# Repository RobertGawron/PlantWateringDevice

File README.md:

# Plant Watering Device

This is a device for watering indoor plants based on the 8-pin PIC10F202-IOT microcontroller.

The goal is to try to make a project on this small MCU and learn how to deal with the limitations of such a small chip, as well as to learn the PIC MCU family ecosystem.

Features:

* **Sensing soil humidity** using a cheap capacitance sensor
* **Display of actual soil humidity and low-level soil humidity when the watering is started;** what is presented on the display is selected by a button, and an additional two LEDs indicate the current reading shown on the display
* Possibility to **change the quantity of water that is dispersed when the soil is detected as dry;** the level can be modified via a button and the current setting is shown on a 10-segment LED bargraph
* Possibility to **select the moisture level when the soil is considered dry** and the watering should be started via a potentiometer

## Software

The software is written in C (C99 with _Static_assert from C11).

[Software details.](./Software/README.md)

## Formal Verification

The watering logic is formally verified using frama-c to mathematically prove correctness properties such as:

* Watering is **never activated** when soil moisture is above the threshold
* Watering **always stops** after the configured duration
* No integer overflows or out-of-bounds array accesses occur

This provides stronger guarantees than testing alone — instead of checking specific inputs, it exhaustively verifies **all possible** input combinations.

## Simulation

The software can be run in a web browser to speed up development (no need to flash the device, soil humidity can be simulated as wanted, etc.).

[Simulation details.](./Simulation/README.md)

## Hardware

[Hardware details.](./Hardware/README.md)

Design tools: KiCad

## Mechanical

In order to keep the pump, PCB, display, and potentiometer in one place, a simple 3D printed holder was made.

[Mechanical specifications and assembly details.](./Mechanic/README.md)

Design tools: OpenSCAD and FreeCad

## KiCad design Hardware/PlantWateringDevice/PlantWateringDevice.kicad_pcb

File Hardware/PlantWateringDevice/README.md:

# Purpose

This section describes the electronic circuit of this device.

# Tools

The circuit was made in KiCad.

# Used modules

These cheap modules were used in this device; they or their clones are available on AliExpress or similar sites:
* 0.28 Inch LED Digital Display DC Voltmeter 0-100V 2.5-30V
* JSB1523006 DC 5V 6V 030 Mini Vacuum Pump Air Pump Oxygen Pump Diaphragm Pump Current 80mA 60KPa 0.6L/min
* Capacitive Soil Moisture Sensor Module Corrosion Resistant Wide Voltage Wire Analog Capacitive Soil Moisture Sensor V1.2

# Electronic diagrams

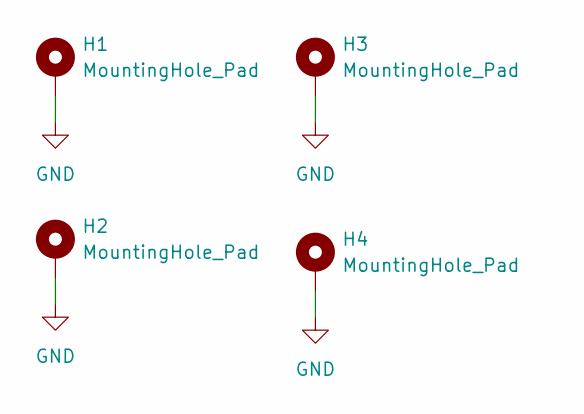
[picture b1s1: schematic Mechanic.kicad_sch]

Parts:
H1, H2, H3, H4: MountingHole_Pad; MountingHole_2.5mm_Pad

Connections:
GND: H1.1 (1_1), H2.1 (1_1), H3.1 (1_1), H4.1 (1_1); also elsewhere on the board

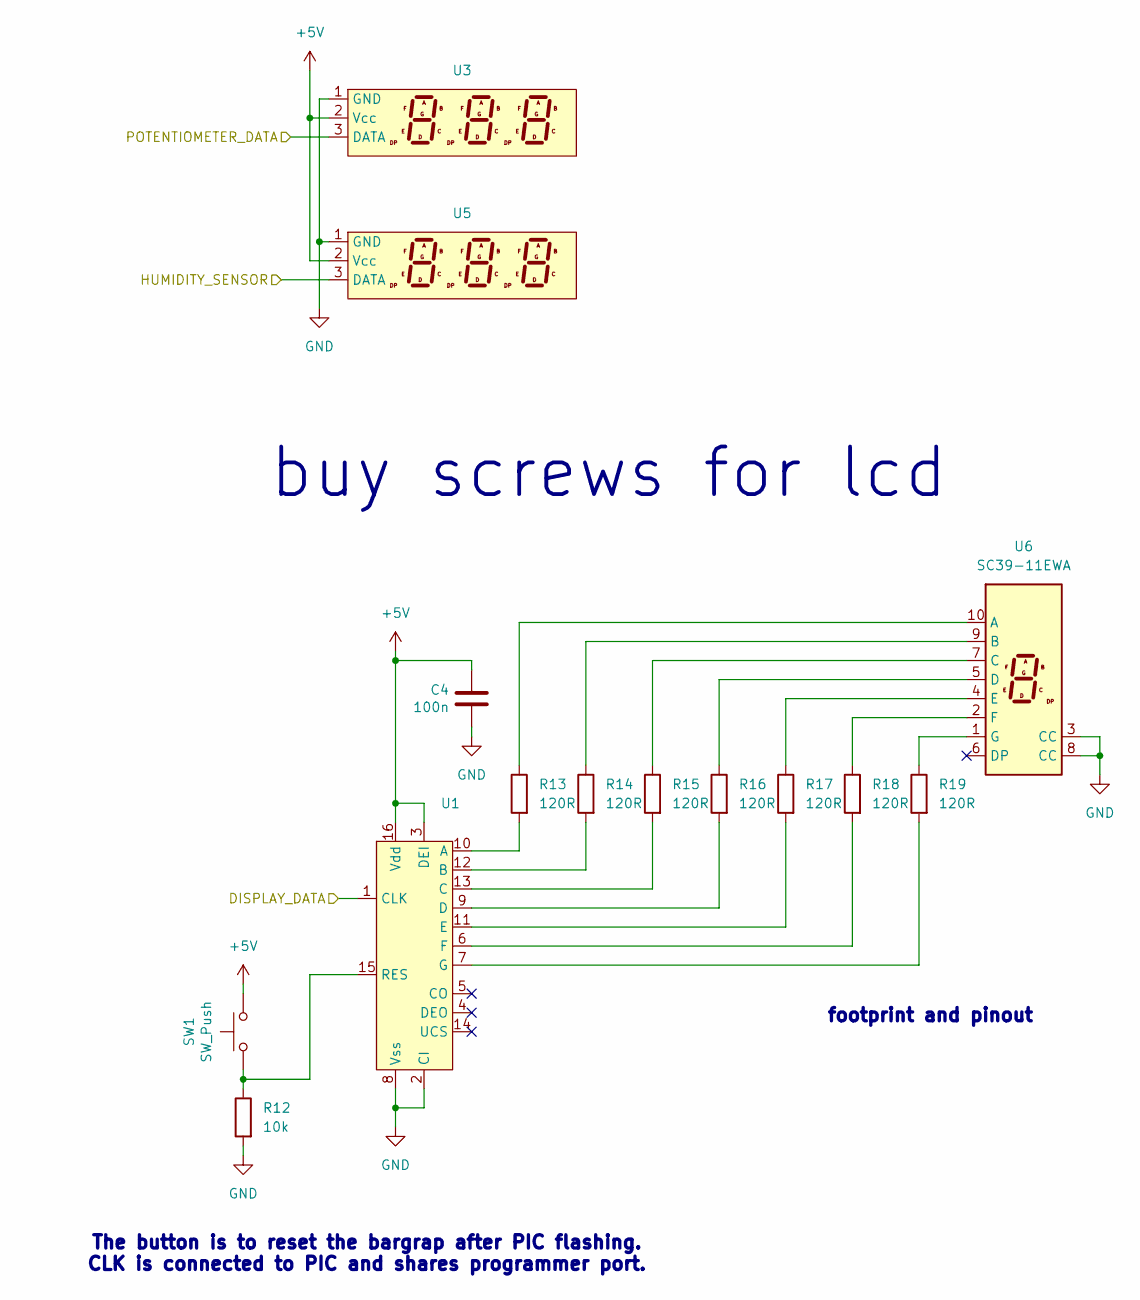
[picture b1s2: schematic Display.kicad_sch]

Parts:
C4: 100n; C_0603_1608Metric
R12: 10k; R_0603_1608Metric
R13, R14, R15, R16, R17, R18, R19: 120R; R_0603_1608Metric
SW1: SW_Push; SW_SPST_PTS645Sx43SMTR92
U1: JEITA_SOIC-16_3.9x9.9mm_P1.27mm
U3, U5: SegmentDisplayMounting
U6: SC39-11EWA; Sx39-1xxxxx

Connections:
+5V: C4.1, SW1.2, U1.3 (DEI), U1.16 (Vdd), U3.2 (Vcc), U5.2 (Vcc); also elsewhere on the board
/DataHandling/DISPLAY_DATA: U1.1 (CLK); also elsewhere on the board
/Display/HUMIDITY_SENSOR: U5.3 (DATA); also elsewhere on the board
/Display/POTENTIOMETER_DATA: U3.3 (DATA); also elsewhere on the board
GND: C4.2, R12.2, U1.2 (CI), U1.8 (Vss), U3.1 (GND), U5.1 (GND), U6.3 (CC), U6.8 (CC); also elsewhere on the board
unnamed: R13.2, U1.10 (A)
unnamed: R14.2, U1.12 (B)
unnamed: R15.2, U1.13 (C)
unnamed: R16.2, U1.9 (D)
unnamed: R17.2, U1.11 (E)
unnamed: R18.2, U1.6 (F)
unnamed: R19.2, U1.7 (G)
unnamed: R12.1, SW1.1, U1.15 (RES)
unnamed: R13.1, U6.10 (A)
unnamed: R14.1, U6.9 (B)
unnamed: R15.1, U6.7 (C)
unnamed: R16.1, U6.5 (D)
unnamed: R17.1, U6.4 (E)
unnamed: R18.1, U6.2 (F)
unnamed: R19.1, U6.1 (G)

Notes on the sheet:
footprint and pinout
buy screws for lcd
The button is to reset the bargrap after PIC flashing. CLK is connected to PIC and shares programmer port.

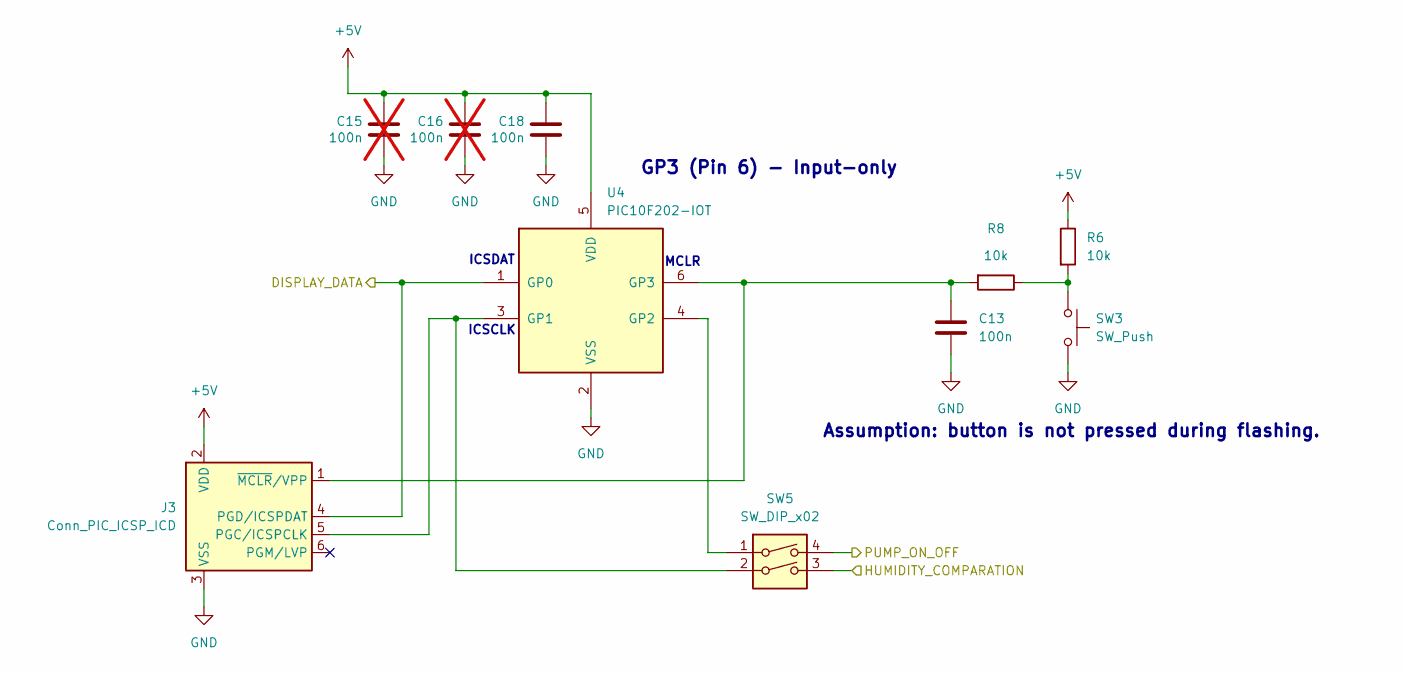
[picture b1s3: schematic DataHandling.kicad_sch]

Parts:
C13, C18: 100n; C_0603_1608Metric
C15, C16: 100n; C_0603_1608Metric; not fitted
J3: Conn_PIC_ICSP_ICD; PinHeader_1x06_P2.54mm_Vertical
R6, R8: 10k; R_0603_1608Metric
SW3: SW_Push; SW_SPST_PTS645Sx43SMTR92
SW5: SW_DIP_x02; DIP-4_W7.62mm
U4: PIC10F202-IOT; SOT-23-6

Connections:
+5V: C15.1, C16.1, C18.1, J3.2 (VDD), R6.1, U4.5 (VDD); also elsewhere on the board
/DataHandling/DISPLAY_DATA: J3.4 (PGD/ICSPDAT), U4.1 (GP0); also elsewhere on the board
/DataHandling/HUMIDITY_COMPARATION: SW5.3; also elsewhere on the board
/DataHandling/PUMP_ON_OFF: SW5.4; also elsewhere on the board
GND: C13.2, C15.2, C16.2, C18.2, J3.3 (VSS), SW3.1, U4.2 (VSS); also elsewhere on the board
unnamed: J3.5 (PGC/ICSPCLK), SW5.2, U4.3 (GP1)
unnamed: C13.1, J3.1 (~MCLR/VPP), R8.2, U4.6 (GP3)
unnamed: R6.2, R8.1, SW3.2
unnamed: SW5.1, U4.4 (GP2)

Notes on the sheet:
ICSCLK
GP3 (Pin 6) - Input-only
ICSDAT
Assumption: button is not pressed during flashing.
MCLR

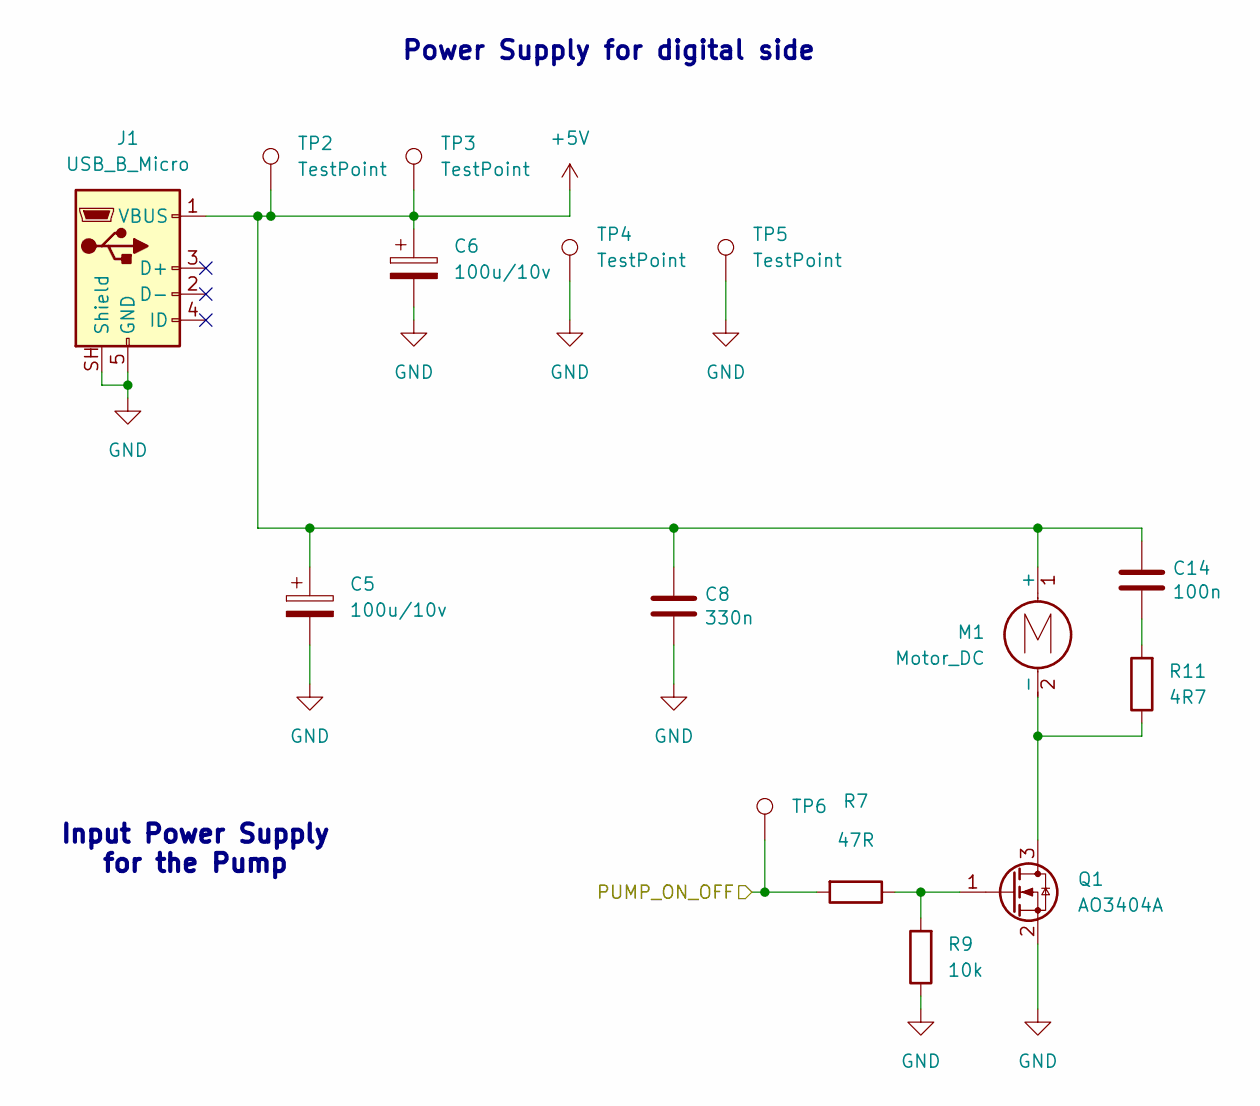
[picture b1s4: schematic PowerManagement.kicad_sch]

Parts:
C5, C6: 100u/10v; CP_EIA-6032-28_Kemet-C
C8: 330n; C_0603_1608Metric
C14: 100n; C_0603_1608Metric
J1: USB_B_Micro; USB_Micro-B_Molex-105017-0001_Extra_Mechanical_Pads
M1: Motor_DC; JST_EH_B2B-EH-A_1x02_P2.50mm_Vertical
Q1: AO3404A; SOT-23
R7: 47R; R_0603_1608Metric
R9: 10k; R_0603_1608Metric
R11: 4R7; R_0603_1608Metric
TP2, TP3, TP4, TP5, TP6: TestPoint; TestPoint_Pad_D1.5mm

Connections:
+5V: C5.1, C6.1, C8.1, C14.1, J1.1 (VBUS), M1.1 (+), TP2.1 (1_1), TP3.1 (1_1); also elsewhere on the board
/DataHandling/PUMP_ON_OFF: R7.2, TP6.1 (1_1); also elsewhere on the board
GND: C5.2, C6.2, C8.2, J1.5 (GND), J1.SH (Shield), Q1.2 (S), R9.1, TP4.1 (1_1), TP5.1 (1_1); also elsewhere on the board
unnamed: C14.2, R11.2
unnamed: M1.2 (-), Q1.3 (D), R11.1
unnamed: Q1.1 (G), R7.1, R9.2

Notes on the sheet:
Power Supply for digital side
Input Power Supply for the Pump

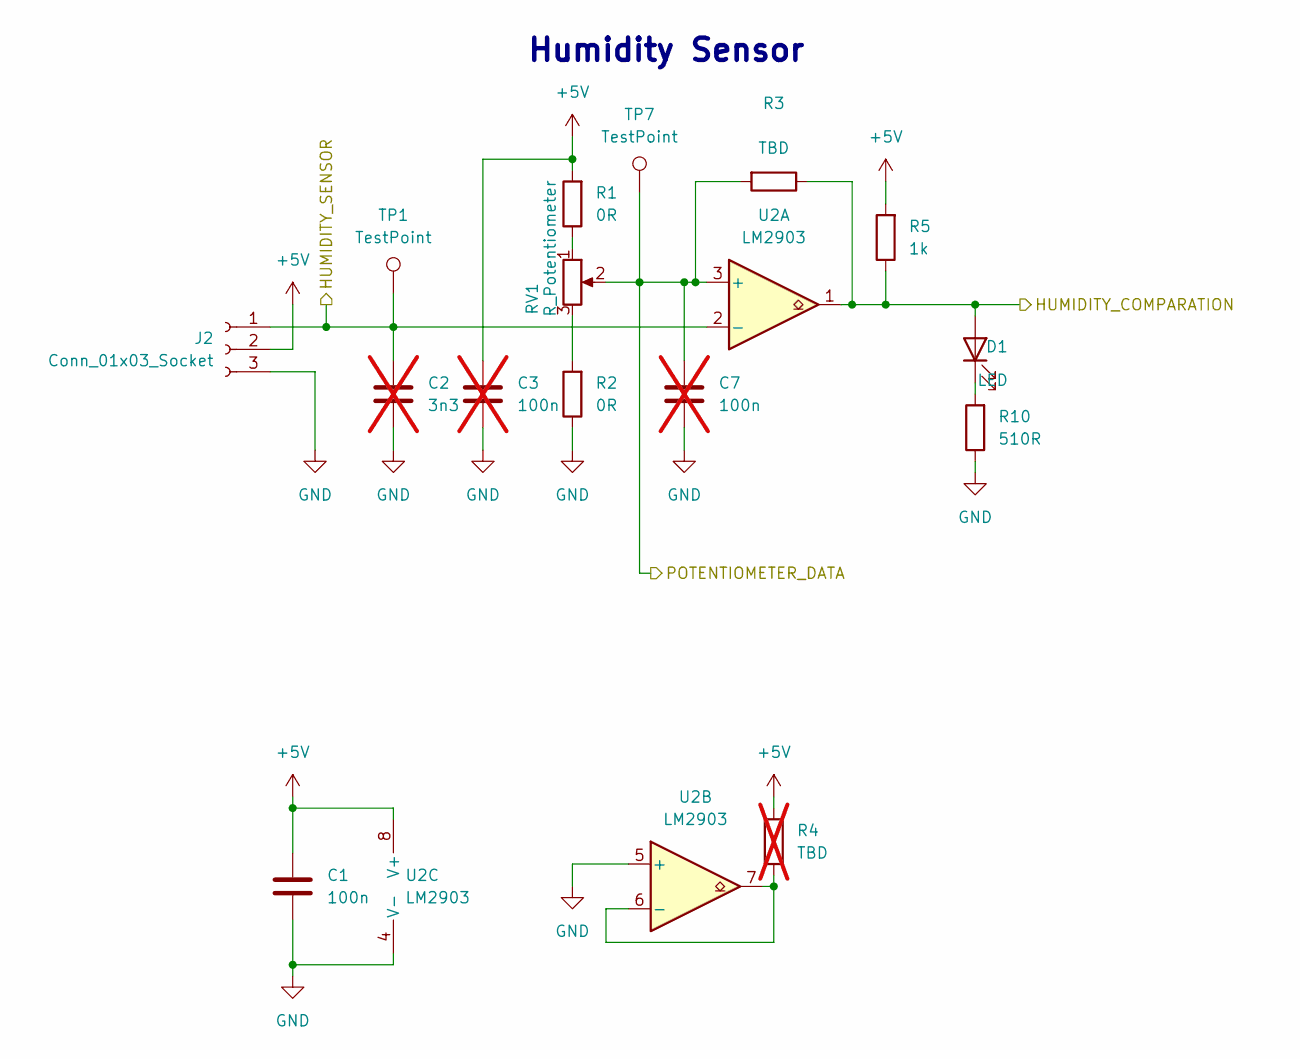
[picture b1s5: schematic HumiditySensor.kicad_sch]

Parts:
C1: 100n; C_0603_1608Metric
C2: 3n3; C_0603_1608Metric; not fitted
C3, C7: 100n; C_0603_1608Metric; not fitted
D1: LED; LED_D4.0mm
J2: Conn_01x03_Socket; JST_EH_B3B-EH-A_1x03_P2.50mm_Vertical
R1, R2: 0R; R_0603_1608Metric
R3: TBD; R_0603_1608Metric
R4: TBD; R_0603_1608Metric; not fitted
R5: 1k; R_0603_1608Metric
R10: 510R; R_0603_1608Metric
RV1: R_Potentiometer; Potentiometer_Alps_RK09L_Single_Vertical
TP1, TP7: TestPoint; TestPoint_Pad_D1.5mm
U2: LM2903; TSSOP-8_3x3mm_P0.65mm

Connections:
+5V: C1.1, C3.1, J2.2, R1.2, R4.2, R5.2, U2.8 (V+); also elsewhere on the board
/DataHandling/HUMIDITY_COMPARATION: D1.2 (A), R3.1, R5.1, U2.1; also elsewhere on the board
/Display/HUMIDITY_SENSOR: C2.1, J2.1, TP1.1 (1_1), U2.2 (-); also elsewhere on the board
/Display/POTENTIOMETER_DATA: C7.1, R3.2, RV1.2, TP7.1 (1_1), U2.3 (+); also elsewhere on the board
GND: C1.2, C2.2, C3.2, C7.2, J2.3, R2.1, R10.1, U2.4 (V-), U2.5 (+); also elsewhere on the board
unnamed: D1.1 (K), R10.2
unnamed: R1.1, RV1.1
unnamed: R2.2, RV1.3
unnamed: R4.1, U2.6 (-), U2.7

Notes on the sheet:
Humidity Sensor

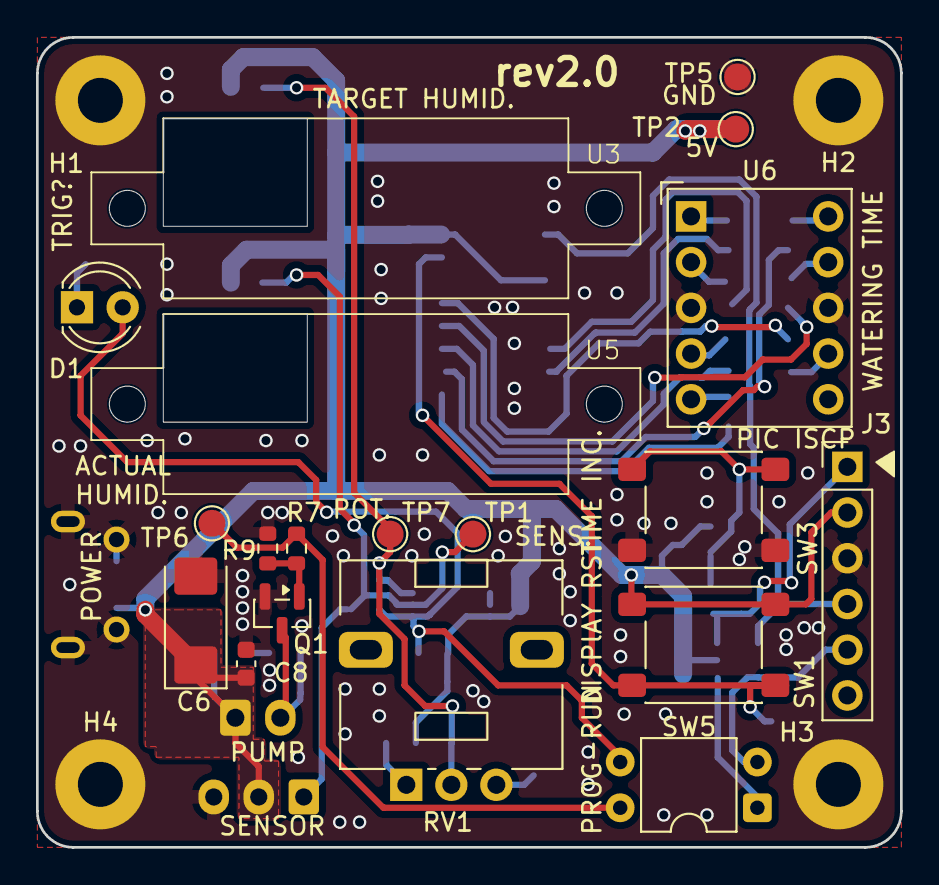
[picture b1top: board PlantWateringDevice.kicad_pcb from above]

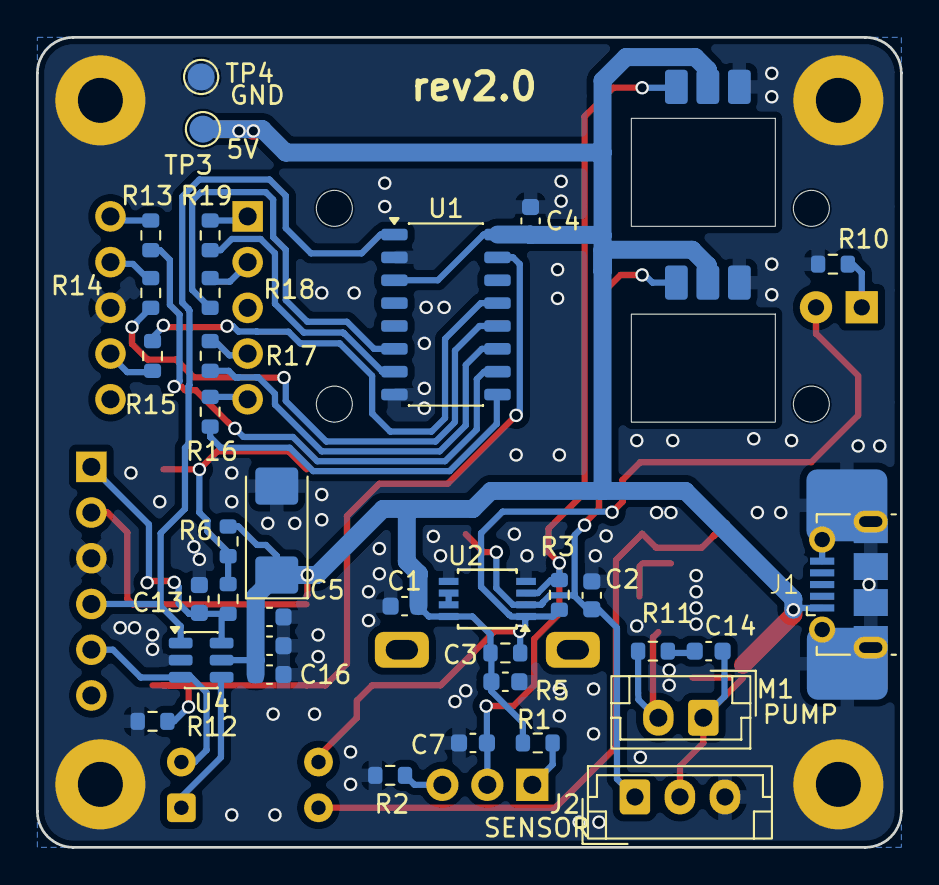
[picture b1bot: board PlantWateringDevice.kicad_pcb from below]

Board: 4 copper layers, 48.0 x 45.0 mm, 58 parts (35 on the bottom side), 33 nets.

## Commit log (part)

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2025-08-10 initial version
2025-09-07 circuit simplification
2025-09-07 model of 3d printed holder
2025-09-13 use openscad for param modeling
2025-09-25 improvements after eric's comments
2025-12-31 fixes before sending pcb and 3d model to production
2026-01-27 cleanup
2026-01-27 README.md cleanup
2026-01-27 firmware implementation
2026-01-27 drv dev
2026-01-30 fix in algo
2026-01-30 fix #29, fix #31
2026-01-30 fix #24, fix #25
2026-01-30 add better device photos
2026-02-22 fix #16, fix #17, fix #18, fix #19, fix #20, fix #26, fix #27, fix #28, fix #30, fix #32, fix#33, fix #34, fix #35, fix #38
2026-02-22 transition to C
2026-03-01 firmware implementation in c, draft of unit tests
2026-03-01 Squashed 'Software/external/unity/' content from commit d1fe18b
    git-subtree-dir: Software/external/unity
    git-subtree-split: d1fe18bd54434efd1ac0dad035d3ab0f8591e086
2026-03-01 readme
2026-03-01 Refactor README for Docker and unit test instructions
    Updated the README to improve clarity and formatting for Docker commands and unit test instructions.
2026-03-01 ut ci draft
2026-03-01 more tests
2026-03-02 before hal
2026-03-02 more simulation files
2026-03-05 draft simu
2026-03-07 js cleanup
2026-03-07 it works
2026-03-08 ts conversion
2026-03-08 web based firmware simulation
2026-03-08 fix display bug, speed up simulation
2026-03-08 try live version
2026-03-09 no cli
2026-03-10 prof
2026-03-13 proof
2026-03-13 add badge
2026-03-14 ci cleanup
2026-03-14 sim build
2026-03-14 pragma
2026-03-14 fix #57, fix #55, fix #49
2026-03-23 fix #64, fix #65, fix #66
2026-03-23 hierarchical block diagram structure in kicad
2026-03-23 fix #67
